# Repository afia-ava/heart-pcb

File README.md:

# Heart PCB

## Components Used
- Red LEDs (16x)
- 330 Ohm resistor (1x)
- 10k Ohm resistor (1x)
- 100k Ohm variable resistor / potentiometer (1x)
- 555 Timer IC (1x)
- 10uF Capacitor (1x)
- Push Button (1x)
- 9V Battery holder clip (1x)

## Journal 
I used KiCad to design this heart shaped PCB. At first, I used the scematic tool to search up all the components I needed and added footprints to them. Then, I imported the design in the PCB editor. I arranged the components somewhat in the heart shape and later drew a heart shape around it on edge.cut layer. After proper placement of all components I moved to F.Cu layer and routed most of the connections. For the ones that overlapped on top, I moved to B.Cu layer and added some vias to connect those routing in the back layer. Throughout the process I ran the Design Rule Check (DRC) form the inspect tool frequently to check out the errors I had. And then we're done!  
  
Made w love,  
*Afia :)*

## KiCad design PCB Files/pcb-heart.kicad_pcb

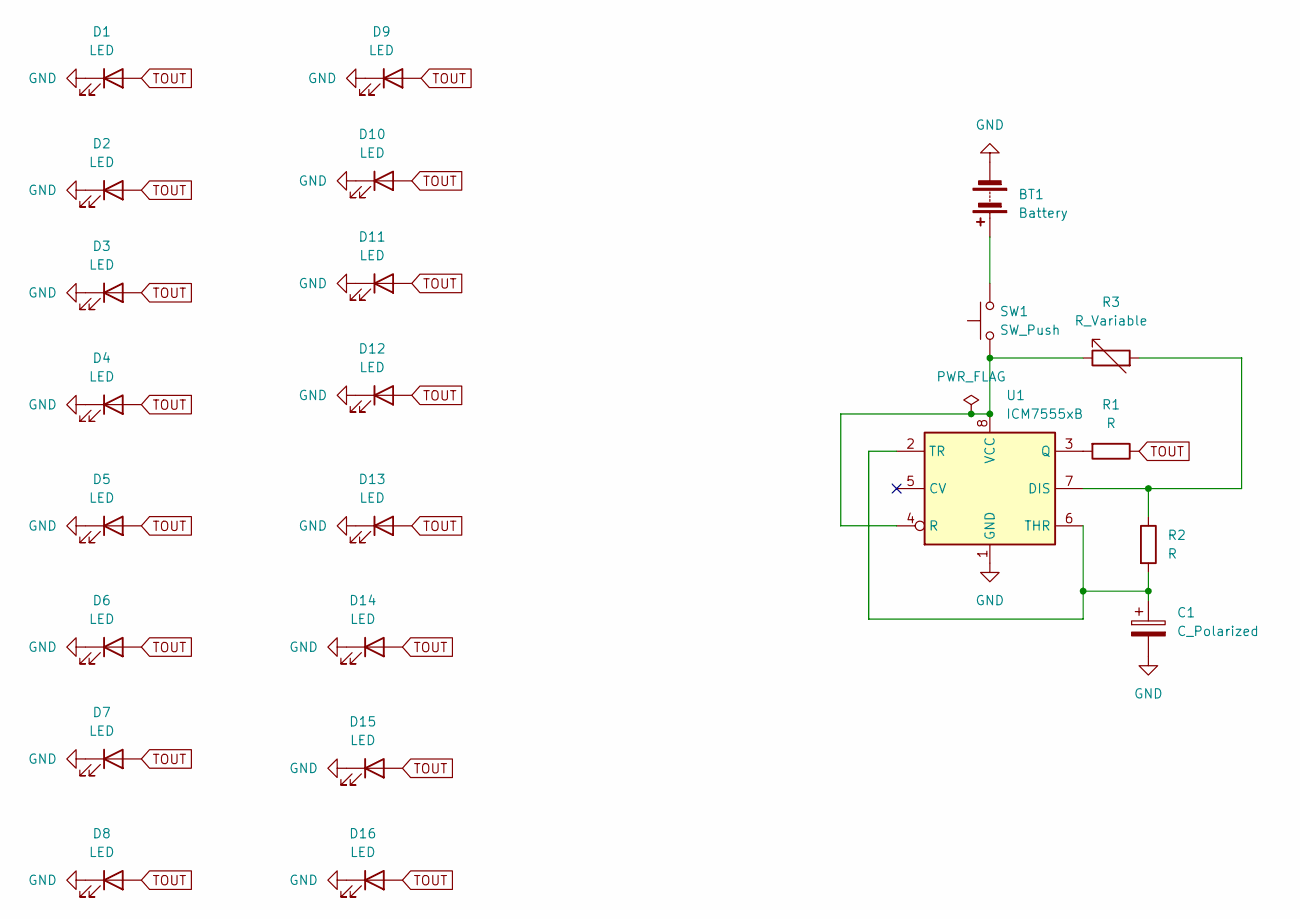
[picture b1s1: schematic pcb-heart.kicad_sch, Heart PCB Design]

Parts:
BT1: Battery; SolderWire-0.1sqmm_1x02_P3.6mm_D0.4mm_OD1mm
C1: C_Polarized; CP_Radial_D5.0mm_P2.50mm
D1, D2, D3, D4, D5, D6, D7, D8, D9, D10, D11, D12, D13, D14, D15, D16: LED; LED_D5.0mm
R1, R2: R; R_Axial_DIN0207_L6.3mm_D2.5mm_P7.62mm_Horizontal
R3: R_Variable; Potentiometer_Bourns_3386P_Vertical
SW1: SW_Push; SW_PUSH_6mm
U1: ICM7555xB; SOIC-8_3.9x4.9mm_P1.27mm

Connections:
GND: BT1.2 (-), C1.2, D1.1 (K), D2.1 (K), D3.1 (K), D4.1 (K), D5.1 (K), D6.1 (K), D7.1 (K), D8.1 (K), D9.1 (K), D10.1 (K), D11.1 (K), D12.1 (K), D13.1 (K), D14.1 (K), D15.1 (K), D16.1 (K), U1.1 (GND)
unnamed: BT1.1 (+), SW1.2
unnamed: R2.1, R3.2, U1.7 (DIS)
unnamed: R1.2, U1.3 (Q)
unnamed: R3.1, SW1.1, U1.4 (R), U1.8 (VCC)
unnamed: C1.1, R2.2, U1.2 (TR), U1.6 (THR)
TOUT: D1.2 (A), D2.2 (A), D3.2 (A), D4.2 (A), D5.2 (A), D6.2 (A), D7.2 (A), D8.2 (A), D9.2 (A), D10.2 (A), D11.2 (A), D12.2 (A), D13.2 (A), D14.2 (A), D15.2 (A), D16.2 (A), R1.1

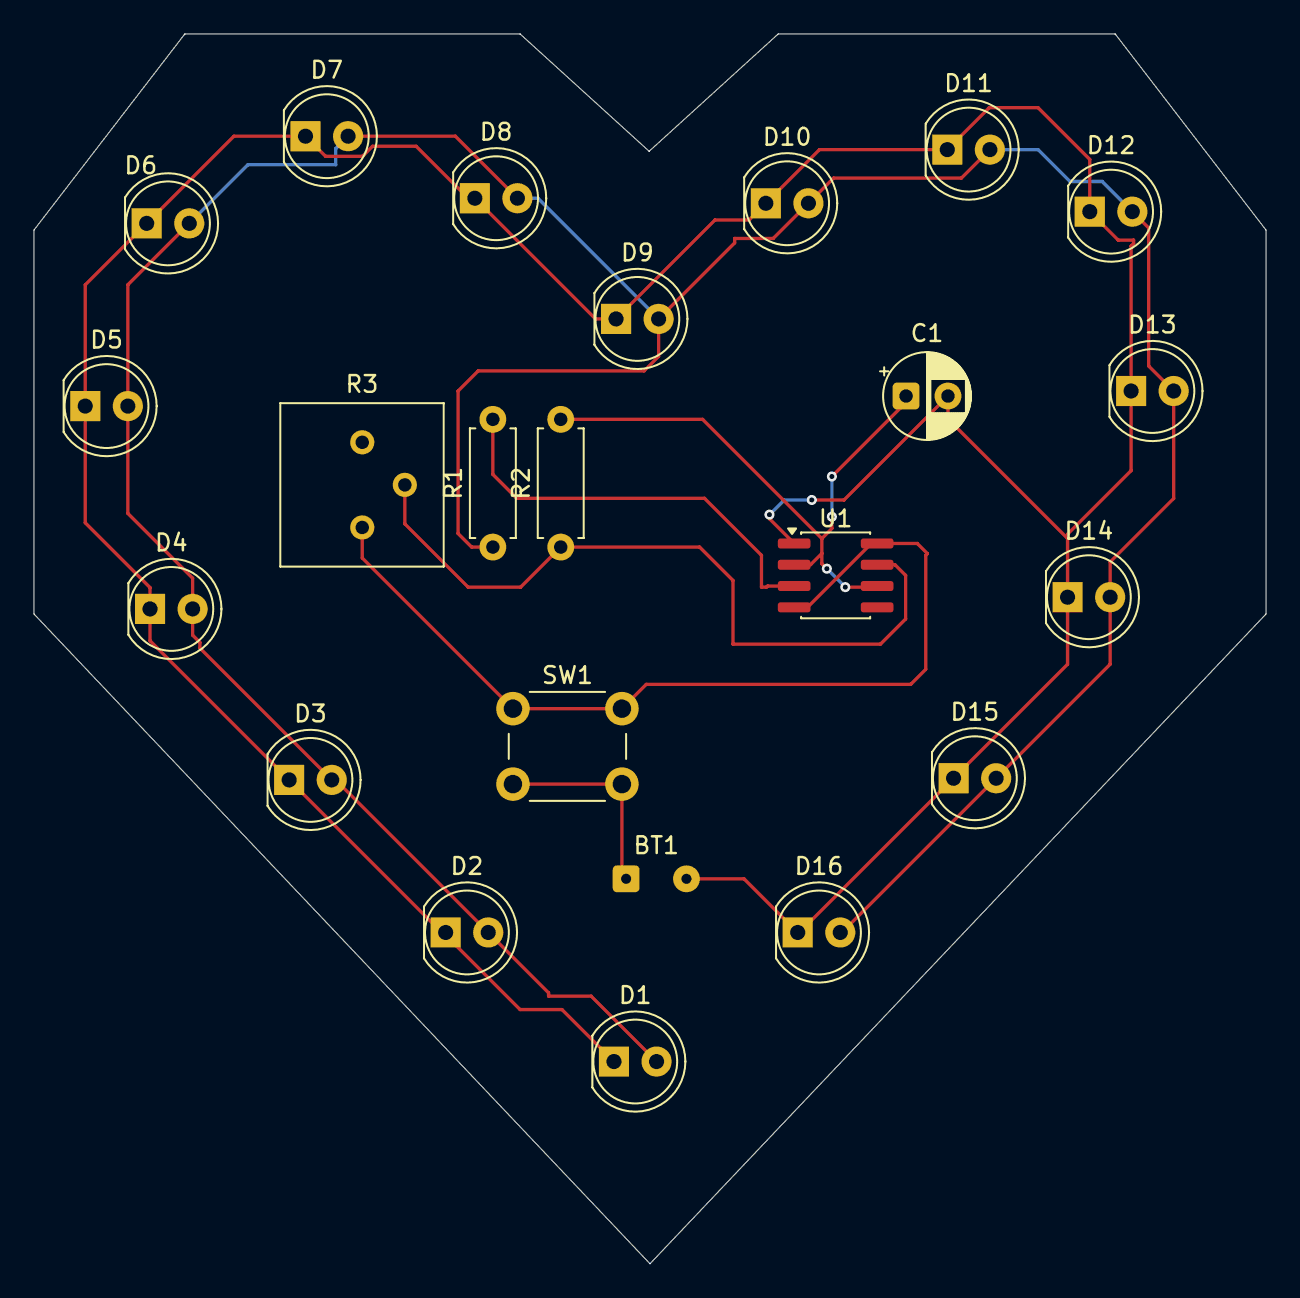
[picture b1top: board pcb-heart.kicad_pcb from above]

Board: 2 copper layers, 73.5 x 73.4 mm, 23 parts (0 on the bottom side), 7 nets.

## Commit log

2026-02-21 add entry
2026-02-21 components list
2026-02-21 entry about PCB design work
2026-02-22 add heart-pcb
2026-02-22 add images and project journal
    Updated component description and added journal section.
2026-02-22 fix spacing
    Updated the journal section for clarity and formatting.
2026-02-22 Create sch
2026-02-22 remove sample
2026-02-22 add folder
2026-06-15 instructions / journal
2026-06-15 add image
2026-06-15 journal images
